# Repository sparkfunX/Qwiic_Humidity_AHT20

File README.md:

SparkFun Qwiic Humidity AHT20
=============================

New from SparkX, the AHT20 breakout board. This low-cost IC triggers temperature and humidity measurements easily over the Qwiic bus you know and love.

SparkFun labored with love to design this board. Feel like supporting open-source hardware?
Buy a [board](https://www.sparkfun.com/) from SparkFun!

Repository Contents
-------------------

* **/Documents** - Datasheet for the AHT20 IC.
* **/Hardware** - Eagle design files (.brd, .sch).
* **/Production** - Production panel files (.brd).

License Information
-------------------

This product is _**open source**_!

Please review the LICENSE.md file for license information.

If you have any questions or concerns regarding our licensing, please contact technical support on our [SparkFun Forum](https://www.sparkfun.com/viewforum.php?f=152).

Distributed as-is; no warranty is given.

- Your friends at SparkFun

_<COLLABORATION CREDIT>_

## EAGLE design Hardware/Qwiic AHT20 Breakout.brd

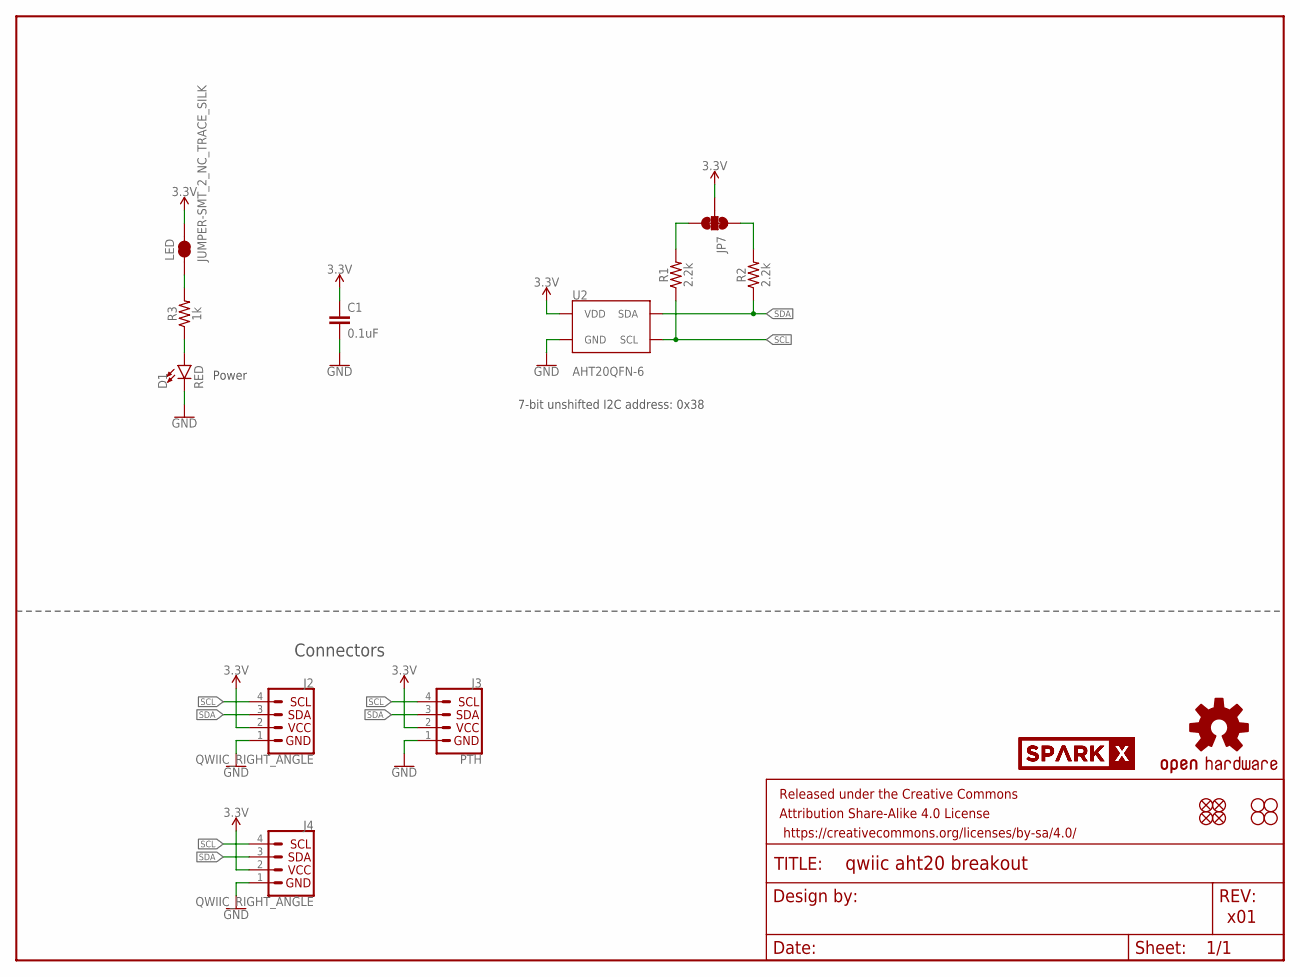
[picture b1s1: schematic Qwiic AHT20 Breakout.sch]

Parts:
C1: 0.1uF; 0603
D1: RED; LED-0603
FRAME1: FRAME-LETTER; CREATIVE_COMMONS
J2, J4: QWIIC_RIGHT_ANGLE; JST04_1MM_RA
J3: PTH; 1X04_NO_SILK
JP1, JP2, JP5, JP6: FIDUCIAL1X2; FIDUCIAL-1X2
JP3, JP4, JP8, JP9: STAND-OFF
JP7: JUMPER-SMT_3_2-NC_TRACE_SILK; SMT-JUMPER_3_2-NC_TRACE_SILK
LED: JUMPER-SMT_2_NC_TRACE_SILK; SMT-JUMPER_2_NC_TRACE_SILK
LOGO1: OSHW-LOGOMINI; OSHW-LOGO-MINI
R1, R2: 2.2k; 0603
R3: 1k; 0603
U2: AHT20QFN-6; QFN-6
U$1, U$2: SPARKX-LOGO4; SPARKX-MEDIUM

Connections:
3.3V: C1.1, J2.2, J3.2 (VCC), J4.2, JP7.2, LED.2, U2.VDD
GND: C1.2, D1.C, J2.1, J3.1 (GND), J4.1, U2.GND
unnamed: JP7.3, R1.2
unnamed: JP7.1, R2.2
unnamed: D1.A, R3.1
unnamed: LED.1, R3.2
SCL: J2.4, J3.4 (SCL), J4.4, R1.1, U2.SCL
SDA: J2.3, J3.3 (SDA), J4.3, R2.1, U2.SDA

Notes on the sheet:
x01
7-bit unshifted I2C address: 0x38
Power
Connectors

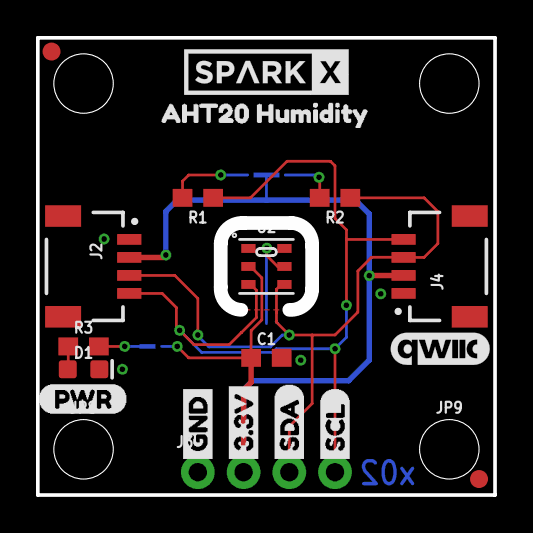
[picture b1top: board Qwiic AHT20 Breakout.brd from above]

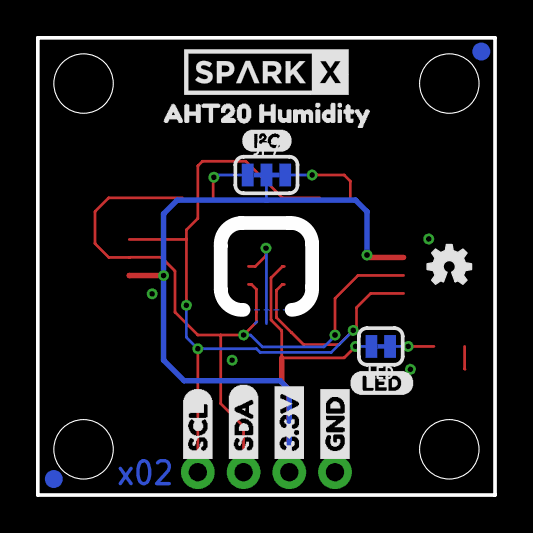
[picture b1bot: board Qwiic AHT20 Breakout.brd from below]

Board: 2 copper layers, 24.8 x 24.8 mm, 38 parts (13 on the bottom side), 8 nets.

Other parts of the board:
U$3, U$22: GND1
U$4, U$21: 3#3V2
U$5, U$27: SDA8
U$6, U$26: SCL9
U$8, U$14: AHT20_HUMIDITY2
U$9: I_SUPER2_C-()-03
U$10: (PWR)
U$11: QWIIC_5.5MM
U$12: LED_32
U$18: ORDERING_INSTRUCTIONS

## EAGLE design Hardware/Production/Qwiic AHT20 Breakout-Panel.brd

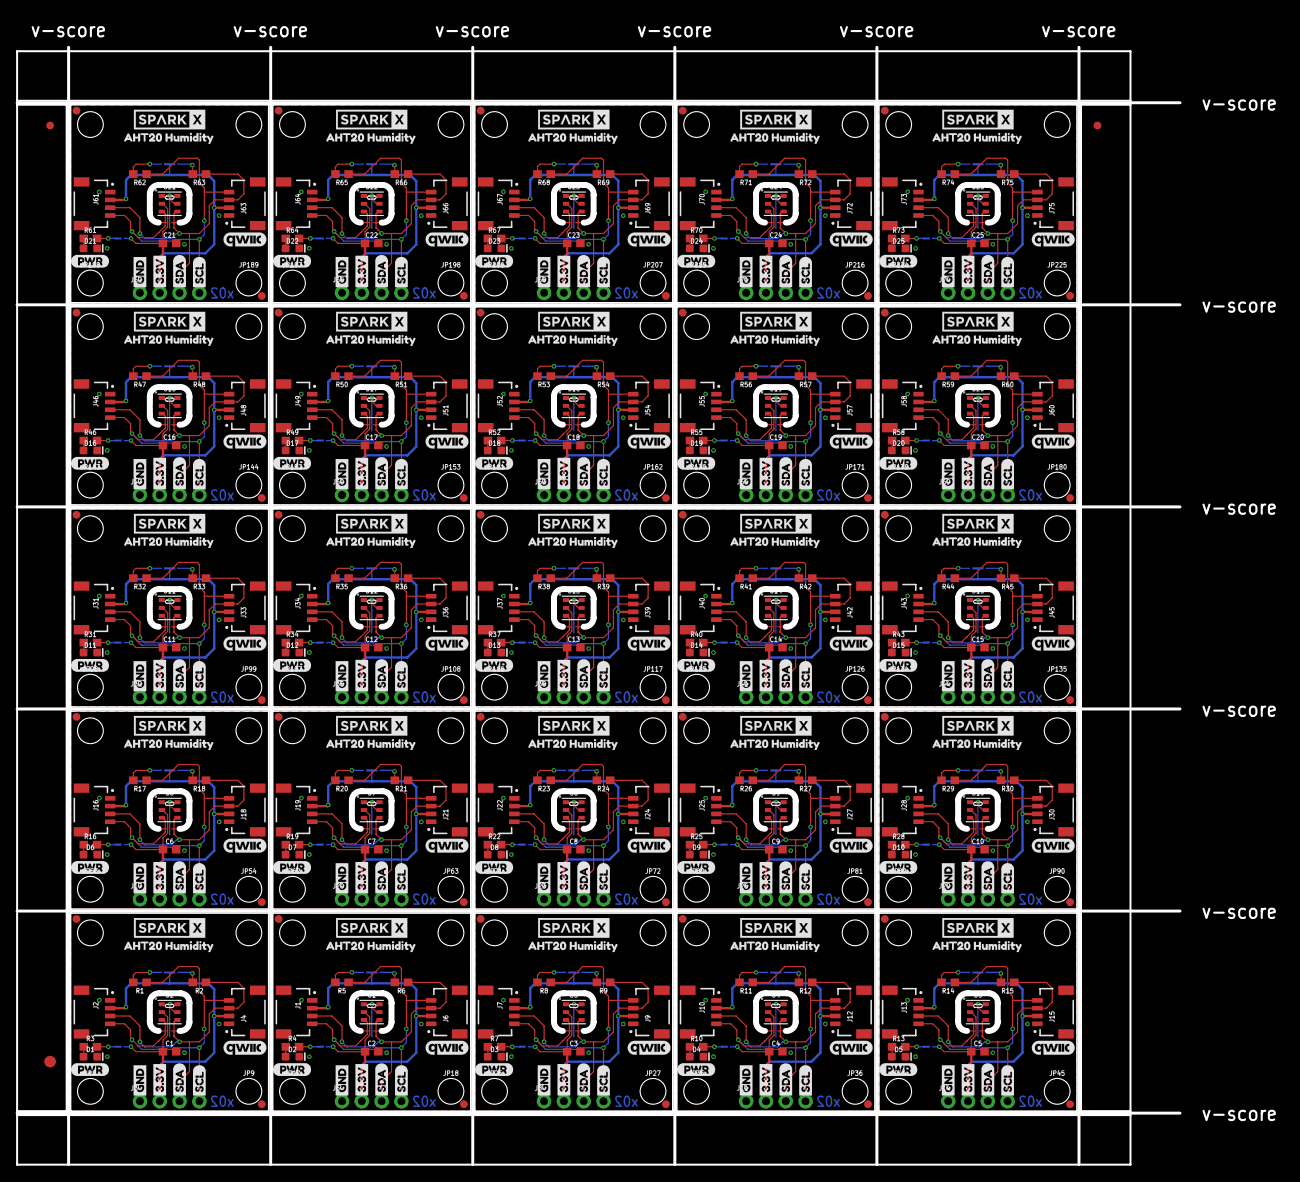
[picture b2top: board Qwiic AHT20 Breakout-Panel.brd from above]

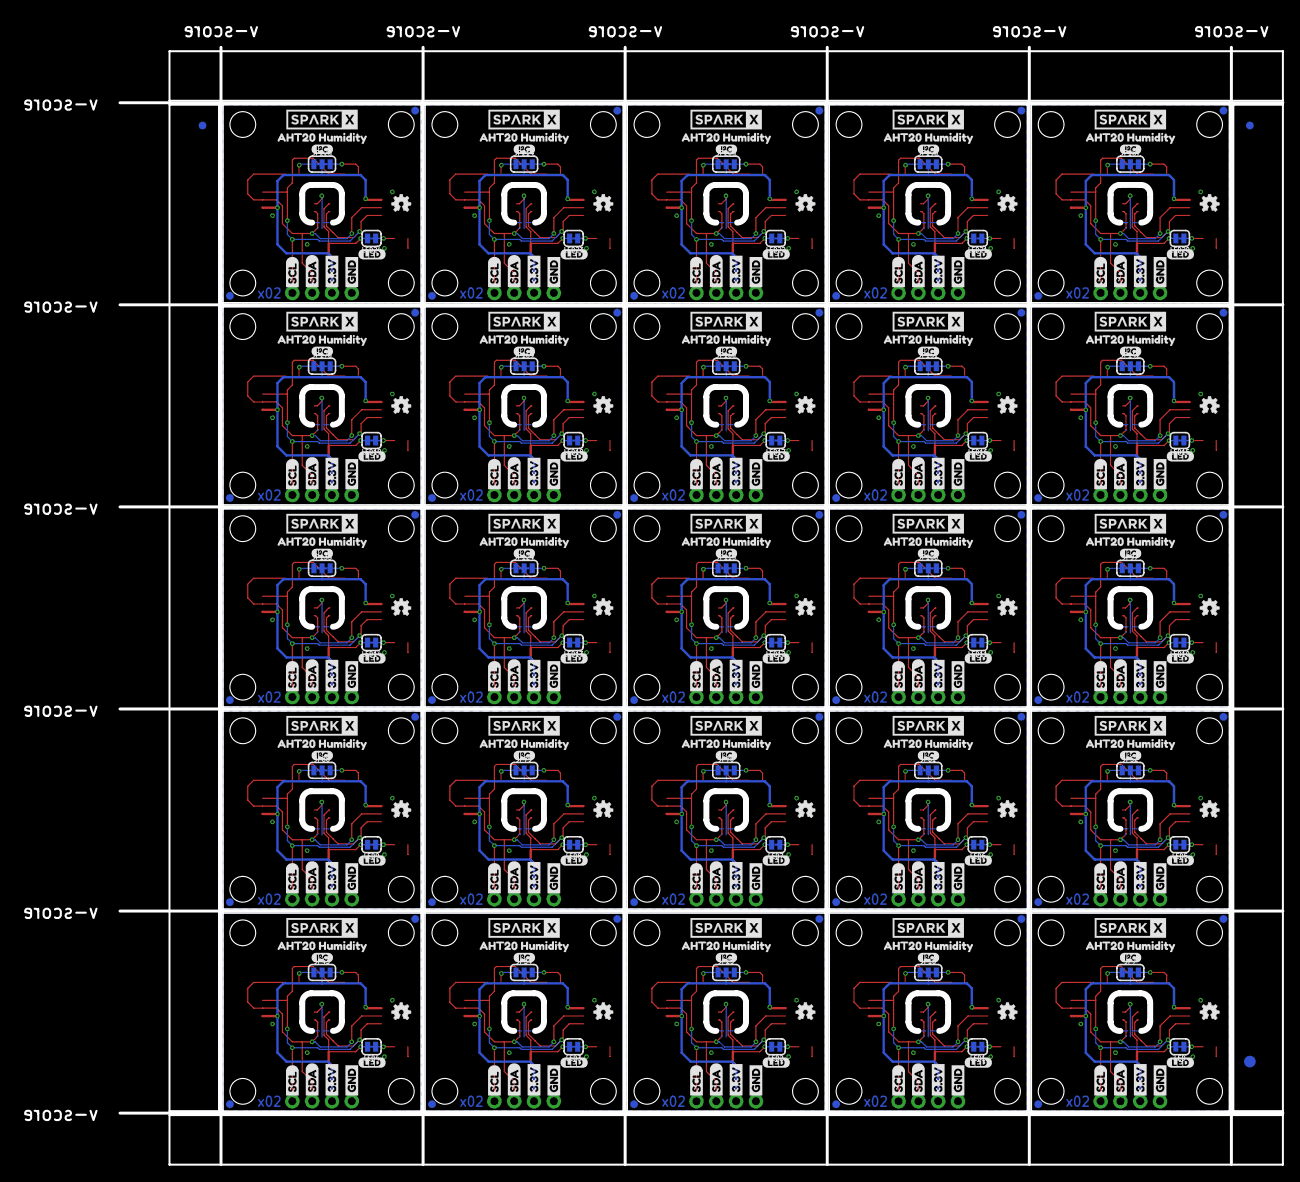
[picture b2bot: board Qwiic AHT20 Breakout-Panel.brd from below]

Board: 2 copper layers, 161.9 x 146.7 mm, 906 parts (328 on the bottom side), 200 nets.

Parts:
C1, C2, C3, C4, C5, C6, C7, C8, C9, C10, C11, C12, C13, C14, C15, C16, C17, C18, C19, C20, C21, C22, C23, C24, C25: 0.1uF; 0603
D1, D2, D3, D4, D5, D6, D7, D8, D9, D10, D11, D12, D13, D14, D15, D16, D17, D18, D19, D20, D21, D22, D23, D24, D25: RED; LED-0603
E$1, E$2, E$3, E$4: FIDUCIAL-1X2
E$5, E$6: FIDUCIAL-1.5X3
J1, J2, J4, J6, J7, J9, J10, J12, J13, J15, J16, J18, J19, J21, J22, J24, J25, J27, J28, J30, J31, J33, J34, J36, J37, J39, J40, J42, J43, J45, J46, J48, J49, J51, J52, J54, J55, J57, J58, J60, J61, J63, J64, J66, J67, J69, J70, J72, J73, J75: QWIIC_RIGHT_ANGLE; JST04_1MM_RA
J3, J5, J8, J11, J14, J17, J20, J23, J26, J29, J32, J35, J38, J41, J44, J47, J50, J53, J56, J59, J62, J65, J68, J71, J74: PTH; 1X04_NO_SILK
JP1, JP2, JP5, JP6, JP12, JP13, JP14, JP15, JP21, JP22, JP23, JP24, JP30, JP31, JP32, JP33, JP39, JP40, JP41, JP42, JP48, JP49, JP50, JP51, JP57, JP58, JP59, JP60, JP66, JP67, JP68, JP69, JP75, JP76, JP77, JP78, JP84, JP85, JP86, JP87, JP93, JP94, JP95, JP96, JP102, JP103, JP104, JP105, JP111, JP112, JP113, JP114, JP120, JP121, JP122, JP123, JP129, JP130, JP131, JP132, JP138, JP139, JP140, JP141, JP147, JP148, JP149, JP150, JP156, JP157, JP158, JP159, JP165, JP166, JP167, JP168, JP174, JP175, JP176, JP177, JP183, JP184, JP185, JP186, JP192, JP193, JP194, JP195, JP201, JP202, JP203, JP204, JP210, JP211, JP212, JP213, JP219, JP220, JP221, JP222: FIDUCIAL1X2; FIDUCIAL-1X2
JP3, JP4, JP8, JP9, JP10, JP11, JP17, JP18, JP19, JP20, JP26, JP27, JP28, JP29, JP35, JP36, JP37, JP38, JP44, JP45, JP46, JP47, JP53, JP54, JP55, JP56, JP62, JP63, JP64, JP65, JP71, JP72, JP73, JP74, JP80, JP81, JP82, JP83, JP89, JP90, JP91, JP92, JP98, JP99, JP100, JP101, JP107, JP108, JP109, JP110, JP116, JP117, JP118, JP119, JP125, JP126, JP127, JP128, JP134, JP135, JP136, JP137, JP143, JP144, JP145, JP146, JP152, JP153, JP154, JP155, JP161, JP162, JP163, JP164, JP170, JP171, JP172, JP173, JP179, JP180, JP181, JP182, JP188, JP189, JP190, JP191, JP197, JP198, JP199, JP200, JP206, JP207, JP208, JP209, JP215, JP216, JP217, JP218, JP224, JP225: STAND-OFF
JP7, JP16, JP25, JP34, JP43, JP52, JP61, JP70, JP79, JP88, JP97, JP106, JP115, JP124, JP133, JP142, JP151, JP160, JP169, JP178, JP187, JP196, JP205, JP214, JP223: JUMPER-SMT_3_2-NC_TRACE_SILK; SMT-JUMPER_3_2-NC_TRACE_SILK
LED, LED1, LED2, LED3, LED4, LED5, LED6, LED7, LED8, LED9, LED10, LED11, LED12, LED13, LED14, LED15, LED16, LED17, LED18, LED19, LED20, LED21, LED22, LED23, LED24: JUMPER-SMT_2_NC_TRACE_SILK; SMT-JUMPER_2_NC_TRACE_SILK
LOGO1, LOGO2, LOGO3, LOGO4, LOGO5, LOGO6, LOGO7, LOGO8, LOGO9, LOGO10, LOGO11, LOGO12, LOGO13, LOGO14, LOGO15, LOGO16, LOGO17, LOGO18, LOGO19, LOGO20, LOGO21, LOGO22, LOGO23, LOGO24, LOGO25: OSHW-LOGOMINI; OSHW-LOGO-MINI
R1, R2, R5, R6, R8, R9, R11, R12, R14, R15, R17, R18, R20, R21, R23, R24, R26, R27, R29, R30, R32, R33, R35, R36, R38, R39, R41, R42, R44, R45, R47, R48, R50, R51, R53, R54, R56, R57, R59, R60, R62, R63, R65, R66, R68, R69, R71, R72, R74, R75: 2.2k; 0603
R3, R4, R7, R10, R13, R16, R19, R22, R25, R28, R31, R34, R37, R40, R43, R46, R49, R52, R55, R58, R61, R64, R67, R70, R73: 1k; 0603
U1, U2, U3, U4, U5, U6, U7, U8, U9, U10, U11, U12, U13, U14, U15, U16, U17, U18, U19, U20, U21, U22, U23, U24, U25: AHT20QFN-6; QFN-6
U$1, U$2, U$7, U$13, U$33, U$34, U$49, U$50, U$65, U$66, U$81, U$82, U$97, U$98, U$113, U$114, U$129, U$130, U$145, U$146, U$161, U$162, U$177, U$178, U$193, U$194, U$209, U$210, U$225, U$226, U$241, U$242, U$257, U$258, U$273, U$274, U$289, U$290, U$305, U$306, U$321, U$322, U$337, U$338, U$353, U$354, U$369, U$370, U$385, U$386: SPARKX-LOGO4; SPARKX-MEDIUM
U$3, U$16, U$19, U$22, U$36, U$39, U$52, U$55, U$68, U$71, U$84, U$87, U$100, U$103, U$116, U$119, U$132, U$135, U$148, U$151, U$164, U$167, U$180, U$183, U$196, U$199, U$212, U$215, U$228, U$231, U$244, U$247, U$260, U$263, U$276, U$279, U$292, U$295, U$308, U$311, U$324, U$327, U$340, U$343, U$356, U$359, U$372, U$375, U$388, U$391: GND1
U$4, U$15, U$20, U$21, U$35, U$40, U$51, U$56, U$67, U$72, U$83, U$88, U$99, U$104, U$115, U$120, U$131, U$136, U$147, U$152, U$163, U$168, U$179, U$184, U$195, U$200, U$211, U$216, U$227, U$232, U$243, U$248, U$259, U$264, U$275, U$280, U$291, U$296, U$307, U$312, U$323, U$328, U$339, U$344, U$355, U$360, U$371, U$376, U$387, U$392: 3#3V2
U$5, U$18, U$23, U$27, U$38, U$41, U$54, U$57, U$70, U$73, U$86, U$89, U$102, U$105, U$118, U$121, U$134, U$137, U$150, U$153, U$166, U$169, U$182, U$185, U$198, U$201, U$214, U$217, U$230, U$233, U$246, U$249, U$262, U$265, U$278, U$281, U$294, U$297, U$310, U$313, U$326, U$329, U$342, U$345, U$358, U$361, U$374, U$377, U$390, U$393: SDA8
U$6, U$17, U$24, U$26, U$37, U$42, U$53, U$58, U$69, U$74, U$85, U$90, U$101, U$106, U$117, U$122, U$133, U$138, U$149, U$154, U$165, U$170, U$181, U$186, U$197, U$202, U$213, U$218, U$229, U$234, U$245, U$250, U$261, U$266, U$277, U$282, U$293, U$298, U$309, U$314, U$325, U$330, U$341, U$346, U$357, U$362, U$373, U$378, U$389, U$394: SCL9
U$8, U$14, U$30, U$32, U$46, U$48, U$62, U$64, U$78, U$80, U$94, U$96, U$110, U$112, U$126, U$128, U$142, U$144, U$158, U$160, U$174, U$176, U$190, U$192, U$206, U$208, U$222, U$224, U$238, U$240, U$254, U$256, U$270, U$272, U$286, U$288, U$302, U$304, U$318, U$320, U$334, U$336, U$350, U$352, U$366, U$368, U$382, U$384, U$398, U$400: AHT20_HUMIDITY2
U$9, U$28, U$44, U$60, U$76, U$92, U$108, U$124, U$140, U$156, U$172, U$188, U$204, U$220, U$236, U$252, U$268, U$284, U$300, U$316, U$332, U$348, U$364, U$380, U$396: I_SUPER2_C-()-03
U$10, U$25, U$43, U$59, U$75, U$91, U$107, U$123, U$139, U$155, U$171, U$187, U$203, U$219, U$235, U$251, U$267, U$283, U$299, U$315, U$331, U$347, U$363, U$379, U$395: (PWR)
U$11, U$29, U$45, U$61, U$77, U$93, U$109, U$125, U$141, U$157, U$173, U$189, U$205, U$221, U$237, U$253, U$269, U$285, U$301, U$317, U$333, U$349, U$365, U$381, U$397: QWIIC_5.5MM
U$12, U$31, U$47, U$63, U$79, U$95, U$111, U$127, U$143, U$159, U$175, U$191, U$207, U$223, U$239, U$255, U$271, U$287, U$303, U$319, U$335, U$351, U$367, U$383, U$399: LED_32

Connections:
3.3V: C1.1, J2.2, J3.2, J4.2, JP7.2, LED.2, U2.VDD
3.3V1: C2.1, J1.2, J5.2, J6.2, JP16.2, LED1.2, U1.VDD
3.3V2: C3.1, J7.2, J8.2, J9.2, JP25.2, LED2.2, U3.VDD
3.3V3: C4.1, J10.2, J11.2, J12.2, JP34.2, LED3.2, U4.VDD
3.3V4: C5.1, J13.2, J14.2, J15.2, JP43.2, LED4.2, U5.VDD
3.3V5: C6.1, J16.2, J17.2, J18.2, JP52.2, LED5.2, U6.VDD
3.3V6: C7.1, J19.2, J20.2, J21.2, JP61.2, LED6.2, U7.VDD
3.3V7: C8.1, J22.2, J23.2, J24.2, JP70.2, LED7.2, U8.VDD
3.3V8: C9.1, J25.2, J26.2, J27.2, JP79.2, LED8.2, U9.VDD
3.3V9: C10.1, J28.2, J29.2, J30.2, JP88.2, LED9.2, U10.VDD
3.3V10: C11.1, J31.2, J32.2, J33.2, JP97.2, LED10.2, U11.VDD
3.3V11: C12.1, J34.2, J35.2, J36.2, JP106.2, LED11.2, U12.VDD
3.3V12: C13.1, J37.2, J38.2, J39.2, JP115.2, LED12.2, U13.VDD
3.3V13: C14.1, J40.2, J41.2, J42.2, JP124.2, LED13.2, U14.VDD
3.3V14: C15.1, J43.2, J44.2, J45.2, JP133.2, LED14.2, U15.VDD
3.3V15: C16.1, J46.2, J47.2, J48.2, JP142.2, LED15.2, U16.VDD
3.3V16: C17.1, J49.2, J50.2, J51.2, JP151.2, LED16.2, U17.VDD
3.3V17: C18.1, J52.2, J53.2, J54.2, JP160.2, LED17.2, U18.VDD
3.3V18: C19.1, J55.2, J56.2, J57.2, JP169.2, LED18.2, U19.VDD
3.3V19: C20.1, J58.2, J59.2, J60.2, JP178.2, LED19.2, U20.VDD
3.3V20: C21.1, J61.2, J62.2, J63.2, JP187.2, LED20.2, U21.VDD
3.3V21: C22.1, J64.2, J65.2, J66.2, JP196.2, LED21.2, U22.VDD
3.3V22: C23.1, J67.2, J68.2, J69.2, JP205.2, LED22.2, U23.VDD
3.3V23: C24.1, J70.2, J71.2, J72.2, JP214.2, LED23.2, U24.VDD
3.3V24: C25.1, J73.2, J74.2, J75.2, JP223.2, LED24.2, U25.VDD
GND: C1.2, D1.C, J2.1, J3.1, J4.1, U2.GND
GND1: C2.2, D2.C, J1.1, J5.1, J6.1, U1.GND
GND2: C3.2, D3.C, J7.1, J8.1, J9.1, U3.GND
GND3: C4.2, D4.C, J10.1, J11.1, J12.1, U4.GND
GND4: C5.2, D5.C, J13.1, J14.1, J15.1, U5.GND
GND5: C6.2, D6.C, J16.1, J17.1, J18.1, U6.GND
GND6: C7.2, D7.C, J19.1, J20.1, J21.1, U7.GND
GND7: C8.2, D8.C, J22.1, J23.1, J24.1, U8.GND
GND8: C9.2, D9.C, J25.1, J26.1, J27.1, U9.GND
GND9: C10.2, D10.C, J28.1, J29.1, J30.1, U10.GND
GND10: C11.2, D11.C, J31.1, J32.1, J33.1, U11.GND
GND11: C12.2, D12.C, J34.1, J35.1, J36.1, U12.GND
GND12: C13.2, D13.C, J37.1, J38.1, J39.1, U13.GND
GND13: C14.2, D14.C, J40.1, J41.1, J42.1, U14.GND
GND14: C15.2, D15.C, J43.1, J44.1, J45.1, U15.GND
GND15: C16.2, D16.C, J46.1, J47.1, J48.1, U16.GND
GND16: C17.2, D17.C, J49.1, J50.1, J51.1, U17.GND
GND17: C18.2, D18.C, J52.1, J53.1, J54.1, U18.GND
GND18: C19.2, D19.C, J55.1, J56.1, J57.1, U19.GND
GND19: C20.2, D20.C, J58.1, J59.1, J60.1, U20.GND
GND20: C21.2, D21.C, J61.1, J62.1, J63.1, U21.GND
GND21: C22.2, D22.C, J64.1, J65.1, J66.1, U22.GND
GND22: C23.2, D23.C, J67.1, J68.1, J69.1, U23.GND
GND23: C24.2, D24.C, J70.1, J71.1, J72.1, U24.GND
GND24: C25.2, D25.C, J73.1, J74.1, J75.1, U25.GND
unnamed: JP7.3, R1.2
unnamed: JP7.1, R2.2
unnamed: D1.A, R3.1
unnamed: LED.1, R3.2
unnamed: D2.A, R4.1
unnamed: JP16.3, R5.2
unnamed: JP16.1, R6.2
unnamed: LED1.1, R4.2
unnamed: D3.A, R7.1
unnamed: JP25.3, R8.2
unnamed: JP25.1, R9.2
unnamed: LED2.1, R7.2
unnamed: D4.A, R10.1
unnamed: JP34.3, R11.2
unnamed: JP34.1, R12.2
unnamed: LED3.1, R10.2
unnamed: D5.A, R13.1
unnamed: JP43.3, R14.2
unnamed: JP43.1, R15.2
unnamed: LED4.1, R13.2
unnamed: D6.A, R16.1
unnamed: JP52.3, R17.2
unnamed: JP52.1, R18.2
unnamed: LED5.1, R16.2
unnamed: D7.A, R19.1
unnamed: JP61.3, R20.2
unnamed: JP61.1, R21.2
unnamed: LED6.1, R19.2
unnamed: D8.A, R22.1
unnamed: JP70.3, R23.2
unnamed: JP70.1, R24.2
unnamed: LED7.1, R22.2
unnamed: D9.A, R25.1
unnamed: JP79.3, R26.2
unnamed: JP79.1, R27.2
unnamed: LED8.1, R25.2
unnamed: D10.A, R28.1
unnamed: JP88.3, R29.2
unnamed: JP88.1, R30.2
unnamed: LED9.1, R28.2
unnamed: D11.A, R31.1
unnamed: JP97.3, R32.2
unnamed: JP97.1, R33.2
unnamed: LED10.1, R31.2
unnamed: D12.A, R34.1
unnamed: JP106.3, R35.2
unnamed: JP106.1, R36.2
unnamed: LED11.1, R34.2
unnamed: D13.A, R37.1
unnamed: JP115.3, R38.2
unnamed: JP115.1, R39.2
unnamed: LED12.1, R37.2
unnamed: D14.A, R40.1
unnamed: JP124.3, R41.2
unnamed: JP124.1, R42.2
unnamed: LED13.1, R40.2
unnamed: D15.A, R43.1
unnamed: JP133.3, R44.2
unnamed: JP133.1, R45.2
unnamed: LED14.1, R43.2
unnamed: D16.A, R46.1
unnamed: JP142.3, R47.2
unnamed: JP142.1, R48.2
unnamed: LED15.1, R46.2
unnamed: D17.A, R49.1
unnamed: JP151.3, R50.2
unnamed: JP151.1, R51.2
unnamed: LED16.1, R49.2
unnamed: D18.A, R52.1
unnamed: JP160.3, R53.2
unnamed: JP160.1, R54.2
unnamed: LED17.1, R52.2
unnamed: D19.A, R55.1
unnamed: JP169.3, R56.2
unnamed: JP169.1, R57.2
unnamed: LED18.1, R55.2
unnamed: D20.A, R58.1
unnamed: JP178.3, R59.2
unnamed: JP178.1, R60.2
unnamed: LED19.1, R58.2
unnamed: D21.A, R61.1
unnamed: JP187.3, R62.2
unnamed: JP187.1, R63.2
unnamed: LED20.1, R61.2
unnamed: D22.A, R64.1
unnamed: JP196.3, R65.2
unnamed: JP196.1, R66.2
unnamed: LED21.1, R64.2
unnamed: D23.A, R67.1
unnamed: JP205.3, R68.2
unnamed: JP205.1, R69.2
unnamed: LED22.1, R67.2
unnamed: D24.A, R70.1
unnamed: JP214.3, R71.2
unnamed: JP214.1, R72.2
unnamed: LED23.1, R70.2
unnamed: D25.A, R73.1
unnamed: JP223.3, R74.2
unnamed: JP223.1, R75.2
unnamed: LED24.1, R73.2
SCL: J2.4, J3.4, J4.4, R1.1, U2.SCL
SCL1: J1.4, J5.4, J6.4, R5.1, U1.SCL
SCL2: J7.4, J8.4, J9.4, R8.1, U3.SCL
SCL3: J10.4, J11.4, J12.4, R11.1, U4.SCL
SCL4: J13.4, J14.4, J15.4, R14.1, U5.SCL
SCL5: J16.4, J17.4, J18.4, R17.1, U6.SCL
SCL6: J19.4, J20.4, J21.4, R20.1, U7.SCL
SCL7: J22.4, J23.4, J24.4, R23.1, U8.SCL
SCL8: J25.4, J26.4, J27.4, R26.1, U9.SCL
SCL9: J28.4, J29.4, J30.4, R29.1, U10.SCL
SCL10: J31.4, J32.4, J33.4, R32.1, U11.SCL
SCL11: J34.4, J35.4, J36.4, R35.1, U12.SCL
SCL12: J37.4, J38.4, J39.4, R38.1, U13.SCL
SCL13: J40.4, J41.4, J42.4, R41.1, U14.SCL
SCL14: J43.4, J44.4, J45.4, R44.1, U15.SCL
SCL15: J46.4, J47.4, J48.4, R47.1, U16.SCL
SCL16: J49.4, J50.4, J51.4, R50.1, U17.SCL
SCL17: J52.4, J53.4, J54.4, R53.1, U18.SCL
SCL18: J55.4, J56.4, J57.4, R56.1, U19.SCL
SCL19: J58.4, J59.4, J60.4, R59.1, U20.SCL
SCL20: J61.4, J62.4, J63.4, R62.1, U21.SCL
SCL21: J64.4, J65.4, J66.4, R65.1, U22.SCL
SCL22: J67.4, J68.4, J69.4, R68.1, U23.SCL
SCL23: J70.4, J71.4, J72.4, R71.1, U24.SCL
SCL24: J73.4, J74.4, J75.4, R74.1, U25.SCL
SDA: J2.3, J3.3, J4.3, R2.1, U2.SDA
SDA1: J1.3, J5.3, J6.3, R6.1, U1.SDA
SDA2: J7.3, J8.3, J9.3, R9.1, U3.SDA
SDA3: J10.3, J11.3, J12.3, R12.1, U4.SDA
SDA4: J13.3, J14.3, J15.3, R15.1, U5.SDA
SDA5: J16.3, J17.3, J18.3, R18.1, U6.SDA
SDA6: J19.3, J20.3, J21.3, R21.1, U7.SDA
SDA7: J22.3, J23.3, J24.3, R24.1, U8.SDA
SDA8: J25.3, J26.3, J27.3, R27.1, U9.SDA
SDA9: J28.3, J29.3, J30.3, R30.1, U10.SDA
SDA10: J31.3, J32.3, J33.3, R33.1, U11.SDA
SDA11: J34.3, J35.3, J36.3, R36.1, U12.SDA
SDA12: J37.3, J38.3, J39.3, R39.1, U13.SDA
SDA13: J40.3, J41.3, J42.3, R42.1, U14.SDA
SDA14: J43.3, J44.3, J45.3, R45.1, U15.SDA
SDA15: J46.3, J47.3, J48.3, R48.1, U16.SDA
SDA16: J49.3, J50.3, J51.3, R51.1, U17.SDA
SDA17: J52.3, J53.3, J54.3, R54.1, U18.SDA
SDA18: J55.3, J56.3, J57.3, R57.1, U19.SDA
SDA19: J58.3, J59.3, J60.3, R60.1, U20.SDA
SDA20: J61.3, J62.3, J63.3, R63.1, U21.SDA
SDA21: J64.3, J65.3, J66.3, R66.1, U22.SDA
SDA22: J67.3, J68.3, J69.3, R69.1, U23.SDA
SDA23: J70.3, J71.3, J72.3, R72.1, U24.SDA
SDA24: J73.3, J74.3, J75.3, R75.1, U25.SDA

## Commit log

2020-04-06 Added HW test sketch
2020-04-13 Got HW example working with brand new HW
    Fixed I2C write/read sequence
    Added debugging print statements
2020-04-29 Generated files for product page
2020-04-29 Correct spacing to 2mm on FP.
2020-04-29 Fix FP of IC to correct 2mm pad spacing
2020-05-01 Fix FP spacing. Remove experimental ADR feature. Update version number.
2020-05-04 Update Qwiic AHT20 Breakout.pdf
    Removed file path comment from bottom of schematic
2021-11-19 Add x02 panel.

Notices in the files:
parts and their libraries:
SparkFun-Resistors: Licensing: Creative Commons ShareAlike 4.0 International - https://creativecommons.org/licenses/by-sa/4.0
SparkFun-Aesthetics: Released under the Creative Commons Attribution Share-Alike 4.0 License
SparkFun-Aesthetics: https://creativecommons.org/licenses/by-sa/4.0
